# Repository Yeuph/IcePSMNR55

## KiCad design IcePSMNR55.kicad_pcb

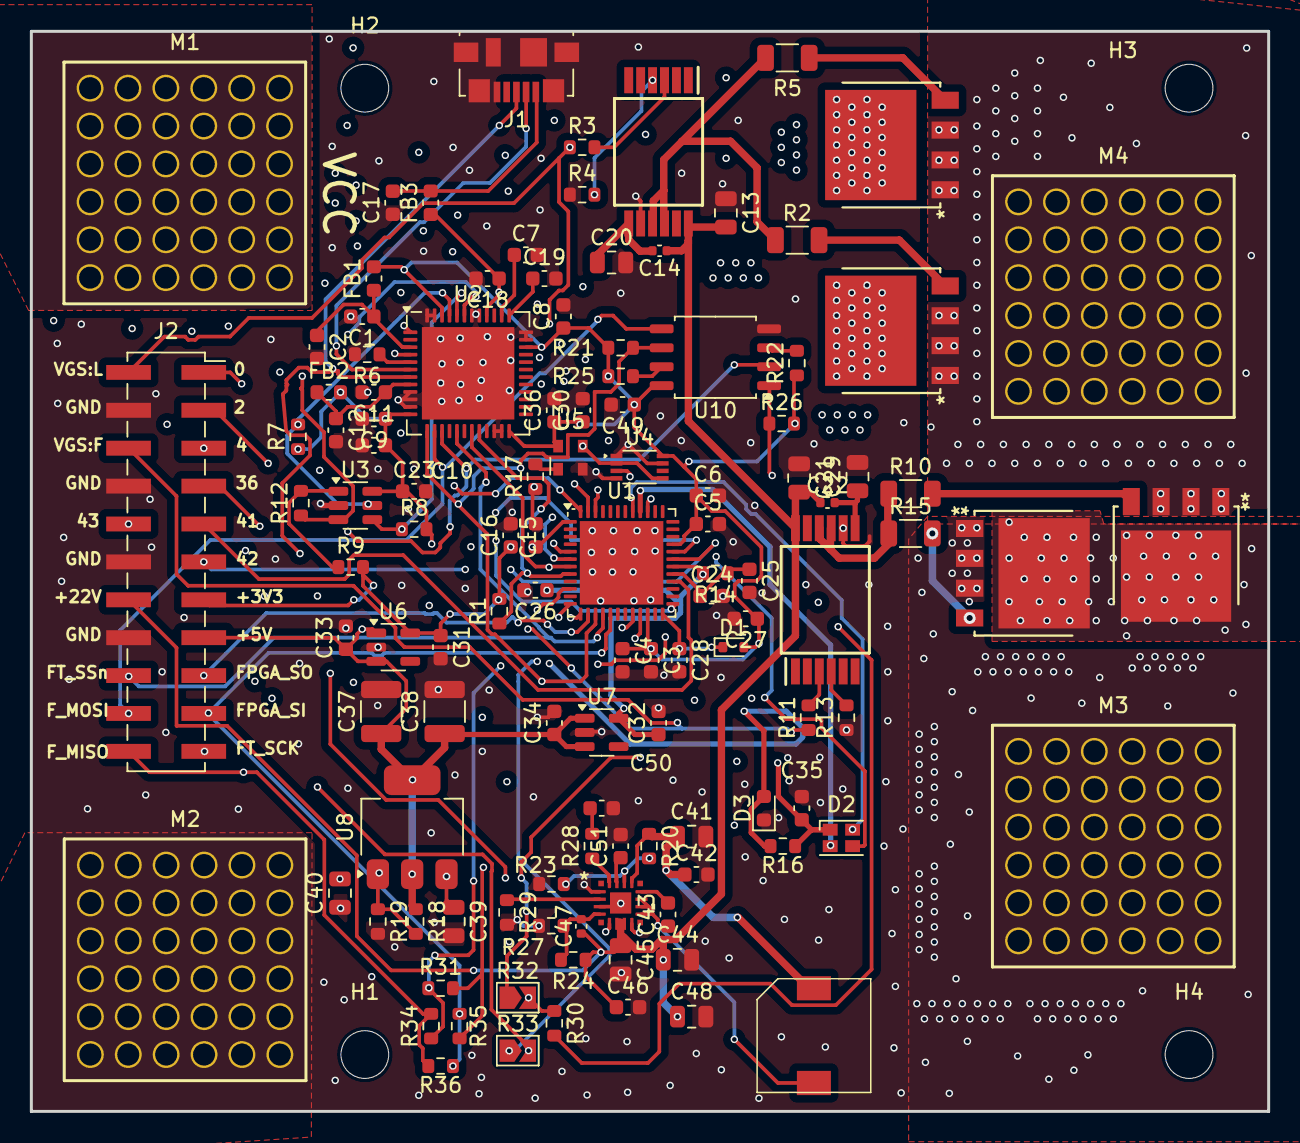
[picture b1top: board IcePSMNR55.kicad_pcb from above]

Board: 8 copper layers, 82.9 x 72.4 mm, 120 parts (0 on the bottom side), 71 nets.

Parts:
C1, C3, C5, C7, C8, C9, C10, C11, C15, C17, C19, C23, C24, C26, C27, C30, C36, C49: 0.1u; C_0603_1608Metric
C2, C4, C6, C12, C16, C18, C25, C28, C31, C32, C33, C34, C35: 4.7u; C_0603_1608Metric
C13, C20, C21, C29, C44, C48: C2012X5R1V226M125AC; C_0805_2012Metric
C14, C22: 0.1uf; C_0402_1005Metric
C37, C38: CL32A157MQVNNNE; C_1210_3225Metric
C39: 10u, 16v+; C_0805_2012Metric
C40: 10u; C_0805_2012Metric
C41: 10u, 50v; C_0805_2012Metric
C42, C43, C46: 1u, 50v; C_0603_1608Metric
C45: 1u, 50v; C_0805_2012Metric
C47: 4.7p, 50v; C_0402_1005Metric
C50: 680p; C_0603_1608Metric
C51: 1u; C_0603_1608Metric
D1: 1N4148WT-7; D_SOD-523
D2: CLMVC-FKA-CLBDGL7LBB79353; LED_Cree-PLCC4_2x2mm_CW
D3: LTST-C191KGKT; LED_0603_1608Metric
FB1, FB2, FB3: BLM18HE152SN1D; L_0603_1608Metric
H1, H2, H3, H4: MountingHole; MountingHole_3.2mm_M3
IC1, IC2: ACFL-3161-000E; Stretched SO12
J1: 47346-0001; USB_Micro-B_Molex_47346-0001
J2: Conn_02x11_Odd_Even; PinSocket_2x11_P2.54mm_Vertical_SMD
L1: 7447783015
M1, M2, M3, M4: 7461061; WP-BUFU_7461061
Q1, Q2, Q3, Q4: PSMNR55-40SSHJ; LFPAK88_SOT1235_NEX-M
R1, R7, R8, R9, R21, R22, R25, R26: 10K; R_0603_1608Metric
R2, R5, R10, R15: 1; R_1206_3216Metric
R3, R4, R11, R13: 120R; R_0603_1608Metric
R6: 12K; R_0603_1608Metric
R12, R16: 2.2K; R_0603_1608Metric
R14: 100; R_0603_1608Metric
R17, R30, R34, R35: DNI; R_0603_1608Metric
R18: 121r; R_0603_1608Metric
R19: 365r; R_0603_1608Metric
R20, R24: 1Meg; R_0603_1608Metric
R23: 330k; R_0603_1608Metric
R27: 45k; R_0603_1608Metric
R28: 20k; R_0603_1608Metric
R29: 47.5k; R_0603_1608Metric
R31, R36: 0; R_0603_1608Metric
R32, R33: OPEN; SolderJumper-2_P1.3mm_Open_TrianglePad1.0x1.5mm
U1: ICE40UP5K-SG48ITR; QFN-48-1EP_7x7mm_P0.5mm_EP5.6x5.6mm
U2: FT232H; QFN-48-1EP_8x8mm_P0.5mm_EP6.2x6.2mm
U3: 93LC56BT-I/OT; SOT-23-6
U4: SN74AUP2G125DCUR; VSSOP-8_2.3x2mm_P0.5mm
U5: SG-210STF 12.0000ML3; Oscillator_SMD_Abracon_ASDMB-4Pin_2.5x2.0mm
U6: AP2127K-3.3; SOT-23-5
U7: AP2127K-1.2; SOT-23-5
U8: LT1117CST#TRPBF; SOT-223-3_TabPin2
U9: LT8337JV-1-PBF; LQFN16_05-08-1798_ADI
U10: W25Q32JVSS; SOIC-8_5.23x5.23mm_P1.27mm

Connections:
+1V2: C26.1, C32.1, R14.2, U1.5 (VCC), U1.30 (VCC), U7.5 (VOUT)
+2V5: C28.1, D1.1 (K), U1.24 (VPP_2V5)
+3V3: C3.1, C4.1, C5.1, C6.1, C8.1, C9.1, C10.1, C15.1, C16.1, C23.1, C27.1, C30.1, C31.1, C35.1, C36.1, C49.1, D1.2 (A), D2.1 (A), FB1.2, FB2.2, J2.13, R1.2, R7.1, R8.2, R9.2, R16.2, R21.2, R22.1, R25.2, R26.2, U1.1 (VCCIO_2), U1.22 (SPI_VCCIO1), U1.33 (VCCIO_0), U2.12 (VCCIO), U2.24 (VCCIO), U2.34 (~RESET), U2.46 (VCCIO), U3.6 (VCC), U4.8 (VCC), U5.4 (Vcc), U6.5 (VOUT), U10.8 (VCC)
+5V: C18.1, C33.1, C34.1, C37.1, C38.1, FB3.1, J2.15, R18.1, U2.40 (VREGIN), U6.1 (VIN), U6.3 (EN), U7.1 (VIN), U7.3 (EN), U8.2 (Out)
/+22V: C13.2, C14.1, C21.2, C22.1, C44.1, C45.1, C46.1, C47.1, C48.1, IC1.12 (VDD), IC2.12 (VDD), J2.14, R24.1, U9.6 (VOUT), U9.7 (VOUT)
/AntiSeriesFB: Q3.5 (D), Q4.5 (D)
/CDONE: D3.2 (A), R16.1, U1.7 (CDONE), U2.19 (ADBUS6)
/CLK_12M_FT: U2.1 (XCSI), U4.2, U4.5, U5.3 (OUT)
/CRESET_N: R1.1, U1.8 (~CRESET), U2.20 (ADBUS7)
/CRYSTAL-IOB_25B_G3: U1.20 (IOB_25b_G3), U4.3
/EE_CLK: R8.1, U2.44 (EECLK), U3.4 (CLK)
/EE_CS: R7.2, U2.45 (EECS), U3.5 (CS)
/EE_DAT: R12.1, U2.43 (EEDATA), U3.3 (DI)
/FLASH_MISO: J2.22, R34.2, R36.1, U2.15 (ADBUS2), U10.2 (DO(IO1))
/FLASH_MOSI: J2.20, R31.2, R35.1, U2.14 (ADBUS1), U10.5 (DI(IO0))
/FPGA_SI: J2.19, R35.2, R36.2, U1.17 (IOB_33b_SPI_SI)
/FPGA_SO: J2.17, R31.1, R34.1, U1.14 (IOB_32a_SPI_SO)
/FT_SCK: J2.21, R21.1, U1.15 (IOB_34a_SPI_SCK), U2.13 (ADBUS0), U10.6 (CLK)
/FT_SSn: J2.18, R26.1, U1.16 (IOB_35b_SPI_SS), U2.17 (ADBUS4), U10.1 (~CS)
/FT_VCORE: C7.1, U2.38 (VCCCORE)
/HighSw: M4.1, M4.2, M4.3, M4.4, M4.5, M4.6, M4.7, M4.8, M4.9, M4.10, M4.11, M4.12, M4.13, M4.14, M4.15, M4.16, M4.17, M4.18, M4.19, M4.20, M4.21, M4.22, M4.23, M4.24, M4.25, M4.26, M4.27, M4.28, M4.29, M4.30, M4.31, M4.32, M4.33, M4.34, M4.35, M4.36, Q1.1 (S), Q1.2 (S), Q1.3 (S), Q2.1 (S), Q2.2 (S), Q2.3 (S), Q3.1 (S), Q3.2 (S), Q3.3 (S)
/IOB_0A: J2.1, U1.46 (IOB_0a)
/IOB_2A: J2.3, U1.47 (IOB_2a)
/IOB_4A: J2.5, U1.48 (IOB_4a)
/IOB_22A: R30.2, U1.12 (IOB_22a)
/IOB_23B: R32.1, U1.21 (IOB_23b)
/IOB_24A: R33.1, U1.13 (IOB_24a)
/IOT_36B: J2.7, U1.25 (IOT_36b)
/IOT_41A: J2.9, U1.28 (IOT_41a)
/IOT_42B: J2.11, U1.31 (IOT_42b)
/IOT_43A: J2.10, U1.32 (IOT_43a)
/LED_B: D2.4 (BK), U1.40 (RGB1)
/LED_G: D2.3 (GK), U1.39 (RGB0)
/LED_R: D2.2 (RK), U1.41 (RGB2)
/USB_M: J1.2 (D-), R33.2, U2.6 (DM)
/USB_P: J1.3 (D+), R30.1, R32.2, U2.7 (DP)
/VCC_PLL: C24.1, C25.1, R14.1, U1.29 (VCCPLL)
/VGS:Fly-IOB_18A: J2.6, R11.1, U1.10 (IOB_18a)
/VGS:LOAD-IOB_13B: J2.2, R3.1, U1.6 (IOB_13b)
/VIN: C39.1, C41.1, C42.1, L1.1, M1.1, M1.2, M1.3, M1.4, M1.5, M1.6, M1.7, M1.8, M1.9, M1.10, M1.11, M1.12, M1.13, M1.14, M1.15, M1.16, M1.17, M1.18, M1.19, M1.20, M1.21, M1.22, M1.23, M1.24, M1.25, M1.26, M1.27, M1.28, M1.29, M1.30, M1.31, M1.32, M1.33, M1.34, M1.35, M1.36, Q1.5 (D), Q2.5 (D), R20.1, U8.3 (In), U9.13 (VIN)
/V_PHY: C1.1, C2.1, FB1.1, U2.3 (VPHY)
/V_PLL: C11.1, C12.1, FB2.1, U2.8 (VPLL)
/V_USB: C17.2, FB3.2, J1.1 (VBUS)
GND: C1.2, C2.2, C3.2, C4.2, C5.2, C6.2, C7.2, C8.2, C9.2, C10.2, C11.2, C12.2, C13.1, C15.2, C16.2, C17.1, C18.2, C19.2, C20.2, C21.1, C23.2, C24.2, C25.2, C26.2, C27.2, C28.2, C29.2, C30.2, C31.2, C32.2, C33.2, C34.2, C35.2, C36.2, C37.2, C38.2, C39.2, C40.1, C41.2, C42.2, C44.2, C45.2, C46.2, C48.2, C49.2, C50.2, C51.2, D3.1 (K), IC1.8 (VS), IC2.8 (VS), J1.5 (GND), J1.6 (Shield), J2.4, J2.8, J2.12, J2.16, M2.1, M2.2, M2.3, M2.4, M2.5, M2.6, M2.7, M2.8, M2.9, M2.10, M2.11, M2.12, M2.13, M2.14, M2.15, M2.16, M2.17, M2.18, M2.19, M2.20, M2.21, M2.22, M2.23, M2.24, M2.25, M2.26, M2.27, M2.28, M2.29, M2.30, M2.31, M2.32, M2.33, M2.34, M2.35, M2.36, M3.1, M3.2, M3.3, M3.4, M3.5, M3.6, M3.7, M3.8, M3.9, M3.10, M3.11, M3.12, M3.13, M3.14, M3.15, M3.16, M3.17, M3.18, M3.19, M3.20, M3.21, M3.22, M3.23, M3.24, M3.25, M3.26, M3.27, M3.28, M3.29, M3.30, M3.31, M3.32, M3.33, M3.34, M3.35, M3.36, Q4.1 (S), Q4.2 (S), Q4.3 (S), R4.1, R6.2, R13.1, R17.1, R19.2, R23.2, R27.2, R29.2, U1.49 (GND), U2.4 (AGND), U2.9 (AGND), U2.10 (GND), U2.11 (GND), U2.22 (GND), U2.23 (GND), U2.35 (GND), U2.36 (GND), U2.41 (AGND), U2.42 (TEST), U2.47 (GND), U2.48 (GND), U2.49 (GND), U3.2 (GND), U4.1, U4.4 (GND), U4.7, U5.2 (GND), U6.2 (GND), U7.2 (GND), U9.1 (SYNC/MODE), U9.3 (GND), U9.5 (GND), U9.8 (GND), U9.17 (GND), U10.4 (GND)
unnamed: C43.1, L1.2, U9.9 (SW), U9.10 (SW), U9.11 (SW)
unnamed: C50.1, R28.2
unnamed: IC1.3 (AN), R3.2
unnamed: IC1.4 (CA), R4.2
unnamed: IC1.9 (VOUTN), IC1.10 (VOUTP), R2.1, R5.1
unnamed: C14.2, C20.1, IC1.7 (VSS)
unnamed: IC2.3 (AN), R11.2
unnamed: IC2.4 (CA), R13.2
unnamed: IC2.9 (VOUTN), IC2.10 (VOUTP), R10.1, R15.1
unnamed: C22.2, C29.1, IC2.7 (VSS)
unnamed: Q1.4 (G), R2.2
unnamed: Q2.4 (G), R5.2
unnamed: Q3.4 (G), R10.2
unnamed: Q4.4 (G), R15.2
unnamed: R6.1, U2.5 (REF)
unnamed: C19.1, U2.37 (VCCA)
unnamed: R9.1, R12.2, U3.1 (DO)
unnamed: R17.2, U5.1 (~ST)
unnamed: C40.2, R18.2, R19.1, U8.1 (GND/ADJ)
unnamed: C43.2, U9.12 (BST)
unnamed: R20.2, R23.1, U9.14 (EN/UVLO)
unnamed: C47.2, R24.2, R27.1, U9.4 (FB)
unnamed: C51.1, U9.15 (INTVCC)
unnamed: R29.1, U9.2 (RT)
unnamed: R28.1, U9.16 (VC)
unnamed: R22.2, U10.3 (IO2)
unnamed: R25.1, U10.7 (IO3)

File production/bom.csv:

Designator,Footprint,Quantity,Value,LCSC Part #
"C1, C10, C11, C15, C17, C19, C23, C24, C26, C27, C3, C30, C36, C49, C7, C8, C9",0603,17,0.1u,
"C12, C16, C18, C2, C25, C28, C31, C32, C33, C34, C35, C4, C6",0603,13,4.7u,
"C13, C20, C21, C29, C44, C48",0805,6,C2012X5R1V226M125AC,
"C14, C22",0402,2,0.1uf,
"C37, C38",1210,2,CL32A157MQVNNNE,
C39,0805,1,"10u, 16v+",
C40,0805,1,10u,
C41,0805,1,"10u, 50v",
"C42, C43, C46",0603,3,"1u, 50v",
C45,0805,1,"1u, 50v",
C47,0402,1,"4.7p, 50v",
C5,0603,1,0.1u,C1005X5R0J104K050BA
C50,0603,1,680p,
C51,0603,1,1u,
D1,D_SOD-123,1,1N4148WT-7,
D2,LED_Cree-PLCC4_2x2mm_CW,1,CLMVC-FKA-CLBDGL7LBB79353,
D3,0603,1,LTST-C191KGKT,
"FB1, FB2, FB3",0603,3,BLM18HE152SN1D,
"H1, H2, H3, H4",MountingHole_3.2mm_M3,4,MountingHole,
"IC1, IC2",Stretched SO12,2,ACFL-3161-000E,C17383873
J1,USB_Micro-B_Molex_47346-0001,1,47589-0001,
J2,PinSocket_2x11_P2.54mm_Vertical_SMD,1,Conn_02x11_Odd_Even,
L1,7447783015,1,7447783015,
"M1, M2, M3, M4",WP-BUFU_7461061,4,7461061,
"Q1, Q2, Q3, Q4",LFPAK88_SOT1235_NEX-M,4,PSMNR55-40SSHJ,
"R1, R21, R22, R25, R26, R7, R8, R9",0603,8,10K,
"R10, R15, R2, R5",1206,4,1,
"R11, R13, R3, R4",0603,4,120R,
"R12, R16",0603,2,2.2K,
R14,0603,1,100,
"R17, R30, R34, R35",0603,4,DNI,
R18,0603,1,121r,
R19,0603,1,365r,
"R20, R24",0603,2,1Meg,
R23,0603,1,330k,
R27,0603,1,45k,
R28,0603,1,20k,
R29,0603,1,47.5k,
"R31, R36",0603,2,0,
"R32, R33",SolderJumper-2_P1.3mm_Open_TrianglePad1.0x1.5mm,2,OPEN,
R6,0603,1,12K,
U1,QFN-48-1EP_7x7mm_P0.5mm_EP5.6x5.6mm,1,ICE40UP5K-SG48ITR,
U10,SOIC-8_5.23x5.23mm_P1.27mm,1,W25Q32JVSS,
U2,QFN-48-1EP_8x8mm_P0.5mm_EP6.2x6.2mm,1,FT232H,
U3,SOT-23-6,1,93LC56BT-I/OT,
U4,VSSOP-8_2.3x2mm_P0.5mm,1,SN74AUP2G125DCUR,
U5,Oscillator_SMD_Abracon_ASDMB-4Pin_2.5x2.0mm,1,SG-210STF 12.0000ML3,
U6,SOT-23-5,1,AP2127K-3.3,
U7,SOT-23-5,1,AP2127K-1.2,
U8,SOT-223-3_TabPin2,1,LT1117IST-3.3#PBF,
U9,LQFN16_05-08-1798_ADI,1,LT8337JV-1-PBF,

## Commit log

2025-01-30 Ice40 based high current high side switch.
2025-01-30 Added verilog control files
